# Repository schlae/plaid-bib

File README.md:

# The Plaid Bib - an Ad Lib MCA Clone

**This card uses the P82C611 bus interface chip and will not work with faster
MCA systems. For a more widely-compatible version, use the [Plaid Bib CPLD
version](https://github.com/schlae/plaid-bib-cpld).**

The Plaid Bib is a 100% compatible clone of the Ad Lib MCA sound card. This is
an Ad Lib card designed for Micro Channel Architecture machines, such as the
IBM PS/2 family and other compatibles from NCR, Tandy, Dell, and others.

Here are the design files. The BOM includes Mouser Electronics part numbers for
everything except for the 82C611, YM3812, and YM3014B, all of which are
available from brokers in China such as UTSource.

[Schematic](https://github.com/schlae/plaid-bib/blob/master/PlaidBib.pdf)

[Bill of Materials](https://github.com/schlae/plaid-bib/blob/master/PlaidBib.csv)

[Fab Files](https://github.com/schlae/plaid-bib/blob/master/fab/PlaidBib-fab.zip)

Use caution when obtaining the P82C611 MCA bus interface part. There is another
chip with the same part number from OPTi, except it is a VLB IDE controller and
totally different.

## Fabrication Notes
This is a two-layer board, outer dimensions 6.452in x 3.475in (164mm x 88mm).
Thickness of the board is 0.063in (1.6mm). When ordering the board, specify
a card edge bevel of 20 degrees. The Dwgs.User layer includes a detail with
the dimensions of the bevel.

Ideally you should use selective gold plating for the edge fingers, but this
can get expensive for small orders. ENIG will work but the gold will rub off
pretty quickly.

For the soldermask color, pick whatever you want! The original was green.

## Assembly Notes
You may wish to socket U7, U8, and U4. These sockets are not included in the
BOM. U7 and U8 are the Yamaha synthesizer chips, and it is useful to be able
to swap them out in case you get a bad one. U4 is the PAL; consider using a
socket in case of programming difficulties.

## PAL Notes
There is a programmable logic device that implements the address decoder and an
address bit latch. The original card uses a 16L8, but the Plaid Bib uses a
readily-available Atmel ATF16V8B. Here is the
[WinCUPL source](https://github.com/schlae/plaid-bib/blob/master/pld/plaidbib.pld)
and the resulting 
[JEDEC file](https://github.com/schlae/plaid-bib/blob/master/pld/plaidbib.jed).
You will need a device programmer such as the low-cost TL866A/CS. 

## Bracket
MCA brackets are no longer available. You have a few options:
- Remove the bracket from an existing card, like a token ring card or something
- 3D print the bracket
- Use the card without a bracket at all

If you want to print your own, here are STEP models of the bracket and the
plastic clip.

[Bracket](https://github.com/schlae/plaid-bib/blob/master/mech/MCABracket.STEP)

[Clip](https://github.com/schlae/plaid-bib/blob/master/mech/MCAClip.STEP)

Please note that neither file is designed specifically for 3D printing; they're
meant to match the real hardware exactly. The clip might print just fine, but
the bracket is probably too thin to print well.

## Compatibility

Micro Channel machines operate at a variety of different bus speeds. Only the
slower ones are compatible with the Plaid Bib.

|PS/2 Model|Clock t(ns)|Default transfer(ns)|Extended transfer(ns)| Compatible?|
|-----|-----------|--------------------|---------------------|----------------|
| 50  | 100       | 300/1WS (I/O)      | 300/1WS             | Yes |
| 55  | 62.5      | 250/2WS            | 375/4WS             | Untested |
| 60  | 100       | 300/1WS (I/O)      | 300/1WS             | Yes/untested |
| 65  | 62.5      | 250/2WS            | 375/4WS             | Untested |
| 70  | 50        | 200/2WS            | 300/4WS             | No |
| 80  | 62.5, 50, 40 | 200             | 300                 | No |
| 90  | 40        | 200                | 300                 | No |
| 95  | 40, 30    | 200, 240           | 300, 320            | No |

The YM3812 FM synthesis chip has minimum timings that are somewhat too slow.
For example, the read pulse width minimum spec is 200ns. The 82C611 generates
the read pulse based on the MCA CMD signal, which asserts for only part of the
default transfer cycle. A fast machine like the model 90 has a default transfer
cycle time of 200ns, so CMD is low for only about 90ns. This is too short to
properly read from the FM chip, meaning that Ad Lib auto detect functions will
fail to see the card.

## Installation
You will need the ADF (adapter description file) in order to set up the Plaid
Bib on your MCA computer.

[Plaid Bib ADF](https://github.com/schlae/plaid-bib/blob/master/@70D7.ADF)

Place the file on a 3 1/2" floppy disk. After you install the card and boot
the computer, it will detect that a new card has been installed and prompt
you to insert the reference disk. Do this and follow the prompts. When the
setup utility asks you to insert the option disk, use the one that contains
the ADF file. After the setup utility configures the card, it will prompt
you to reboot the machine.

Once that's finished, try out the Plaid Bib with your favorite game!

## License
This work is licensed under a Creative Commons Attribution-ShareAlike 4.0
International License. See [https://creativecommons.org/licenses/by-sa/4.0/](https://creativecommons.org/licenses/by-sa/4.0/).

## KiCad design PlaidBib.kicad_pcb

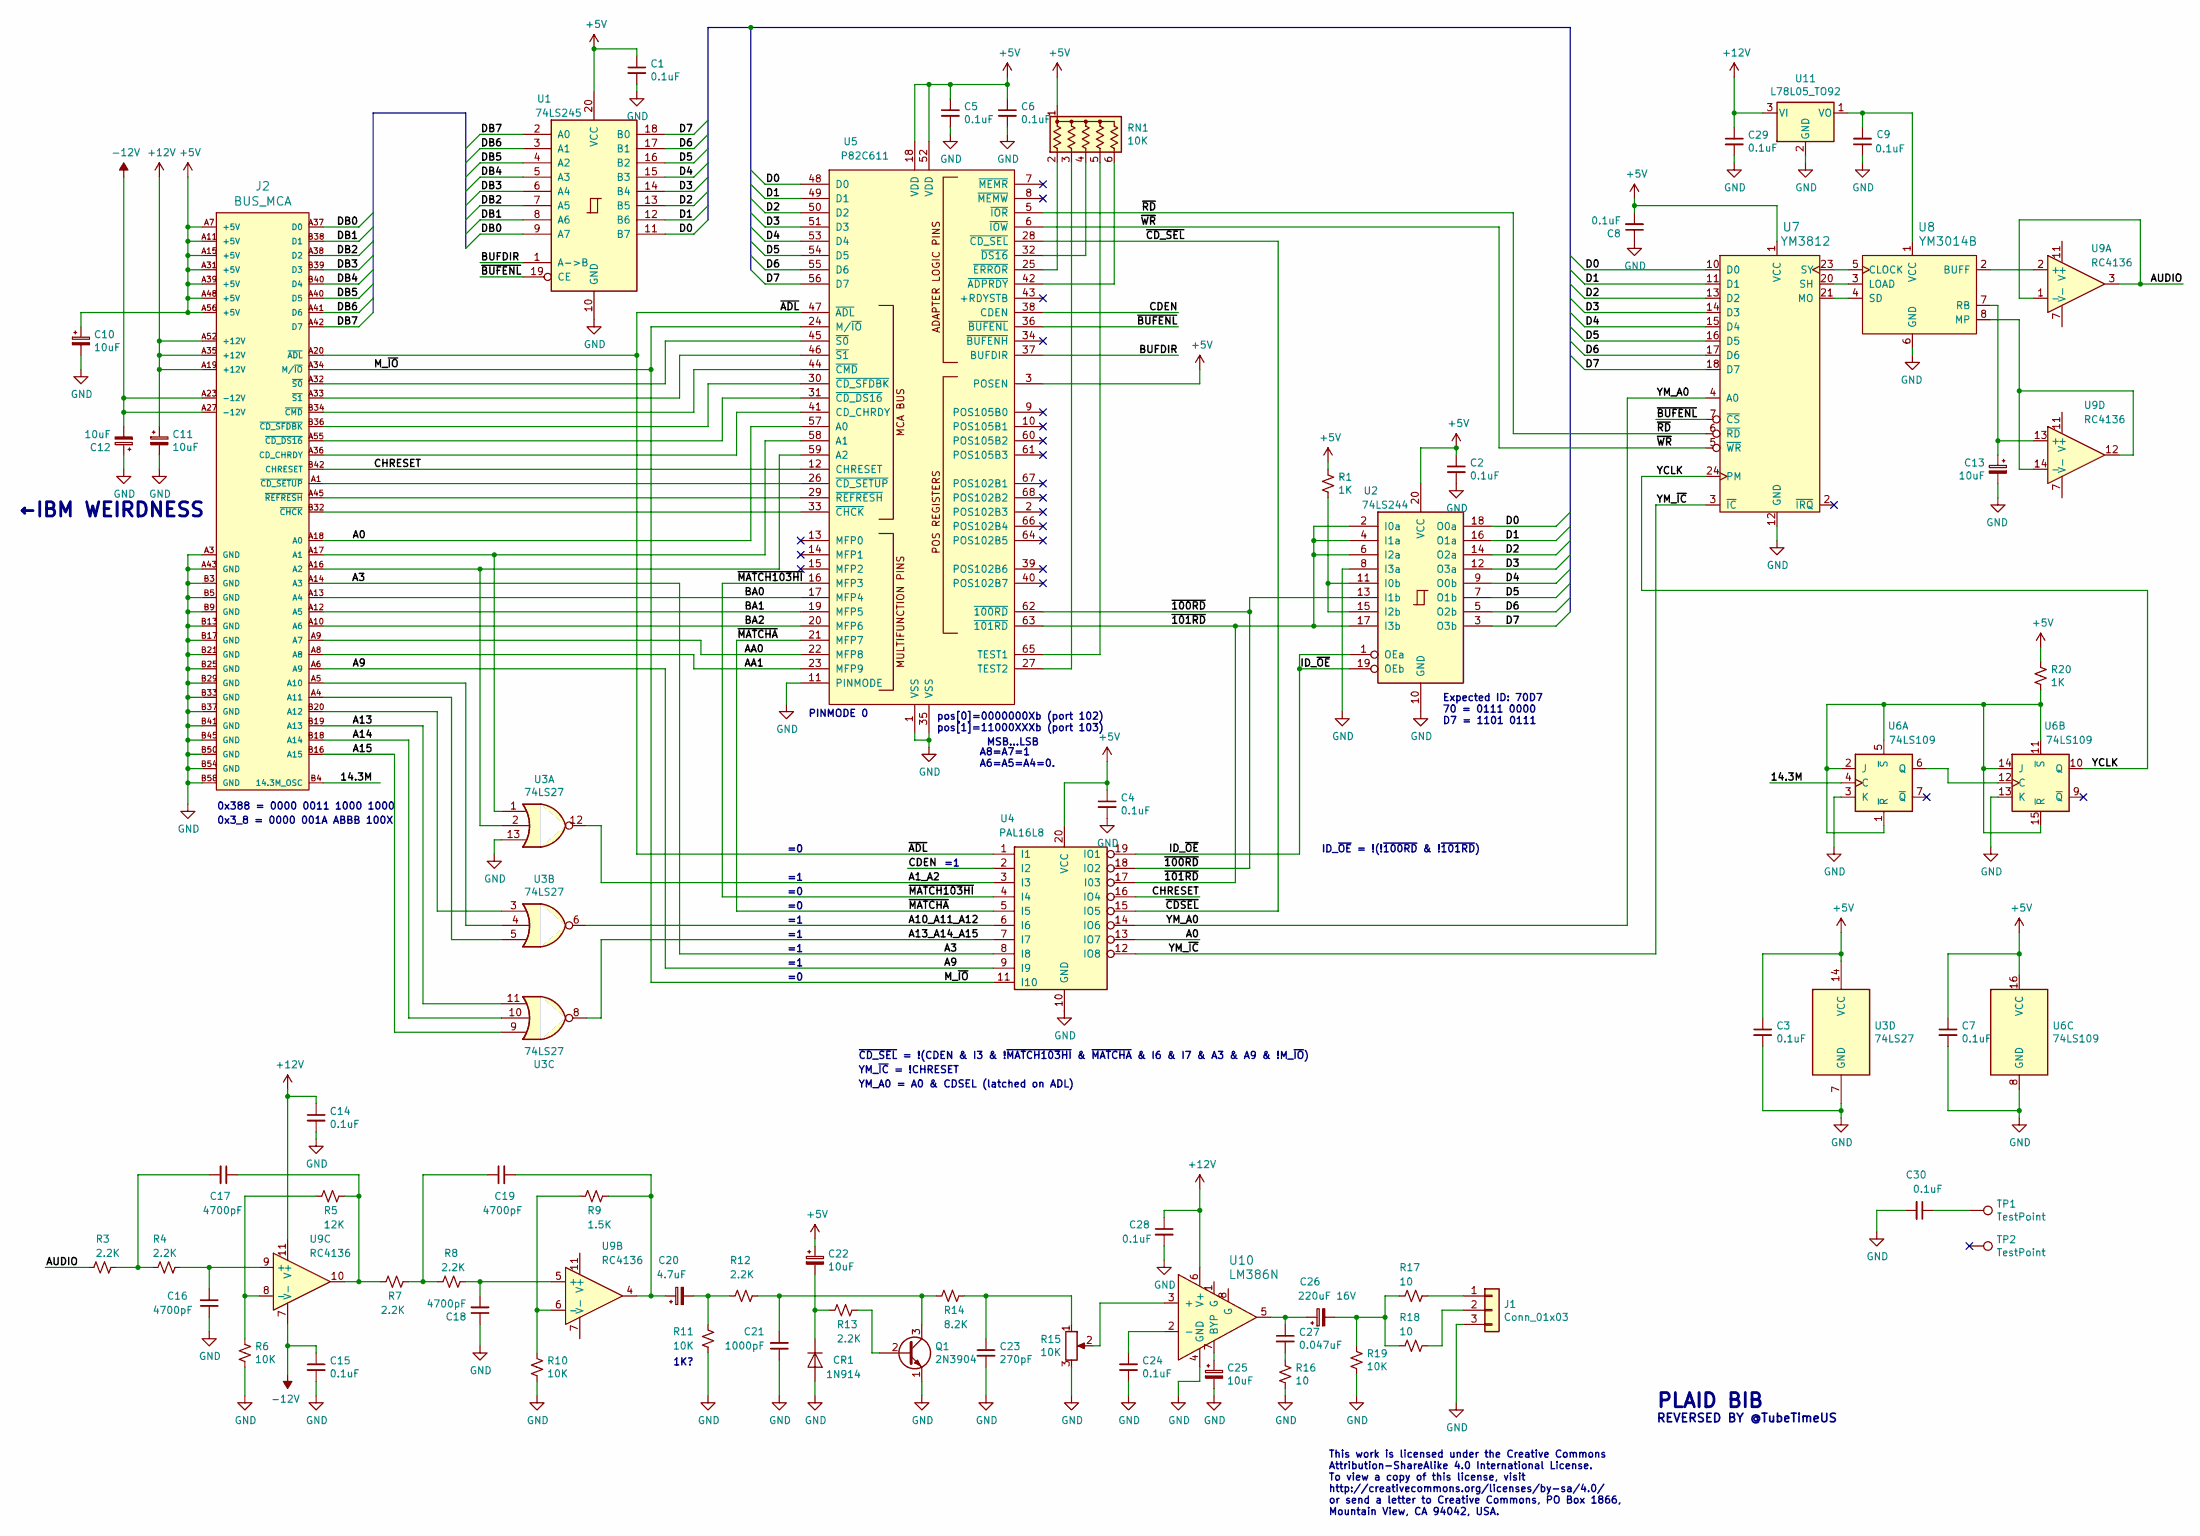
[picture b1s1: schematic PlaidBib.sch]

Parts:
C1, C2, C3, C4, C5, C6, C7, C8, C9, C14, C15, C24, C28, C29, C30: 0.1uF; CAP23; Mouser 581-AR215C104K4R
C10, C11, C12, C13, C22, C25: 10uF; CAPAP200; Mouser 581-TAP106M025CRW
C16, C17, C18, C19: 4700pF; CAP23; Mouser 581-AR211C472K4R
C20: 4.7uF; CAPAP200; Mouser 581-TAP475K016SCS
C21: 1000pF; CAP23; Mouser 581-AR211C102K4R
C23: 270pF; CAP23; Mouser 594-S271K43SL0N6TK5R
C26: 220uF 16V; CAPA1000; Mouser 647-TVX1C221MAD
C27: 0.047uF; CAP23; Mouser 581-AR215C473K4R
CR1: 1N914; DIOA500; Mouser 512-1N914
J1: Conn_01x03; SJ1-3553; Mouser 490-SJ1-3553NG
J2: BUS_MCA; BUS_MCA_ADLIB
Q1: 2N3904; TO92-IL; Mouser 512-2N3904BU
R1, R20: 1K; RESA500; Mouser 291-1K-RC
R3, R4, R7, R8, R12, R13: 2.2K; RESA500; Mouser 291-2.2K-RC
R5: 12K; RESA500; Mouser 291-12K-RC
R6, R10, R11, R19: 10K; RESA500; Mouser 291-10K-RC
R9: 1.5K; RESA500; Mouser 291-1.5K-RC
R14: 8.2K; RESA500; Mouser 291-8.2K-RC
R15: 10K; RK14J11A000G; Mouser 688-RK14J11A000G
R16, R17, R18: 10; RESA500; Mouser 291-10-RC
RN1: 10K; R_Array_SIP6; MPN 4606X-101-103LF; Mouser 652-4606X-1LF-10K
TP1, TP2: TestPoint; MH_125
U1: 74LS245; DIP300_20N; Mouser 595-SN74LS245N
U2: 74LS244; DIP300_20N; Mouser 595-SN74LS244N
U3: 74LS27; DIP300_14N; Mouser 595-SN74LS27N
U4: PAL16L8; DIP300_20N; Mouser 556-AF16V8B15PU
U5: P82C611; PLCC-68_THT-Socket
U6: 74LS109; DIP300_16N; Mouser 595-SN74LS109AN
U7: YM3812; DIP600_24N
U8: YM3014B; DIP300_8N
U9: RC4136; DIP300_14N; Mouser 595-RC4136N
U10: LM386N; DIP300_8N; Mouser 926-LM386N-4/NOPB
U11: L78L05_TO92; TO92-IL; Mouser 511-L78L05ACZ

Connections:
+5V: C1.1, C2.1, C3.1, C4.1, C5.1, C6.1, C7.1, C8.2, C10.1, C22.1, J2.A7 (+5V), J2.A11 (+5V), J2.A15 (+5V), J2.A31 (+5V), J2.A39 (+5V), J2.A48 (+5V), J2.A56 (+5V), R1.1, R20.1, RN1.1 (common), U1.20 (VCC), U2.20 (VCC), U3.14 (VCC), U4.20 (VCC), U5.3 (POSEN), U5.18 (VDD), U5.52 (VDD), U6.16 (VCC), U7.1 (VCC)
+12V: C11.1, C14.1, C28.1, C29.1, J2.A19 (+12V), J2.A35 (+12V), J2.A52 (+12V), U9.11 (V+), U10.6 (V+), U11.3 (VI)
-12V: C12.2, C15.1, J2.A23 (-12V), J2.A27 (-12V), U9.7 (V-)
/14.3M: J2.B4 (14.3M_OSC), U6.4 (C)
/A0: J2.A18 (A0), U4.13 (IO7), U5.57 (A0)
/A1_A2: U3.12, U4.3 (I3)
/A3: J2.A14 (A3), U4.8 (I8)
/A9: J2.A6 (A9), U4.9 (I9)
/A10_A11_A12: U3.6, U4.6 (I6)
/A13: J2.B19 (A13), U3.11
/A13_A14_A15: U3.8, U4.7 (I7)
/A14: J2.B18 (A14), U3.10
/A15: J2.B16 (A15), U3.9
/AA0: J2.A9 (A7), U5.22 (MFP8)
/AA1: J2.A8, U5.23 (MFP9)
/AUDIO: R3.2, U9.1 (-), U9.3
/BA0: J2.A13 (A4), U5.17 (MFP4)
/BA1: J2.A12 (A5), U5.19 (MFP5)
/BA2: J2.A10 (A6), U5.20 (MFP6)
/BUFDIR: U1.1 (A->B), U5.37 (BUFDIR)
/CDEN: U4.2 (I2), U5.38 (CDEN)
/CHRESET: J2.B42 (CHRESET), U4.16 (IO4), U5.12 (CHRESET)
/D0: U1.11 (B7), U2.18 (O0a), U5.48 (D0), U7.10 (D0)
/D1: U1.12 (B6), U2.16 (O1a), U5.49 (D1), U7.11 (D1)
/D2: U1.13 (B5), U2.14 (O2a), U5.50 (D2), U7.13 (D2)
/D3: U1.14 (B4), U2.12 (O3a), U5.51 (D3), U7.14 (D3)
/D4: U1.15 (B3), U2.9 (O0b), U5.53 (D4), U7.15 (D4)
/D5: U1.16 (B2), U2.7 (O1b), U5.54 (D5), U7.16 (D5)
/D6: U1.17 (B1), U2.5 (O2b), U5.55 (D6), U7.17 (D6)
/D7: U1.18 (B0), U2.3 (O3b), U5.56 (D7), U7.18 (D7)
/DB0: J2.A37 (D0), U1.9 (A7)
/DB1: J2.B38 (D1), U1.8 (A6)
/DB2: J2.A38 (D2), U1.7 (A5)
/DB3: J2.B39 (D3), U1.6 (A4)
/DB4: J2.B40 (D4), U1.5 (A3)
/DB5: J2.A40 (D5), U1.4 (A2)
/DB6: J2.A41 (D6), U1.3 (A1)
/DB7: J2.A42 (D7), U1.2 (A0)
/ID_~OE: U2.1 (OEa), U2.19 (OEb), U4.19 (IO1)
/M_~IO: J2.A34 (M/~IO), U4.11 (I10), U5.24 (M/~IO)
/YCLK: U6.10 (Q), U7.24 (PM)
/YM_A0: U4.14 (IO6), U7.4 (A0)
/YM_~IC: U4.12 (IO8), U7.3 (~IC)
/~100RD: U2.13 (I1b), U4.18 (IO2), U5.62 (~100RD)
/~101RD: U2.2 (I0a), U2.4 (I1a), U2.6 (I2a), U2.17 (I3b), U4.17 (I03), U5.63 (~101RD)
/~ADL: J2.A20 (~ADL), U4.1 (I1), U5.47 (~ADL)
/~BUFENL: U1.19 (CE), U5.36 (~BUFENL), U7.7 (~CS)
/~CDSEL: U4.15 (IO5), U5.28 (~CD_SEL)
/~MATCH103HI: U4.4 (I4), U5.16 (MFP3)
/~MATCHA: U4.5 (I5), U5.21 (MFP7)
/~RD: U5.5 (~IOR), U7.6 (~RD)
/~WR: U5.6 (~IOW), U7.5 (~WR)
GND: C1.2, C2.2, C3.2, C4.2, C5.2, C6.2, C7.2, C8.1, C9.1, C10.2, C11.2, C12.1, C13.2, C14.2, C15.2, C16.2, C18.1, C21.1, C23.2, C24.2, C25.2, C28.2, C29.2, C30.2, CR1.2 (A), J1.3, J2.A3 (GND), J2.A43 (GND), J2.B3 (GND), J2.B5 (GND), J2.B9 (GND), J2.B13 (GND), J2.B17 (GND), J2.B21 (GND), J2.B25 (GND), J2.B29 (GND), J2.B33 (GND), J2.B37 (GND), J2.B41 (GND), J2.B45 (GND), J2.B50 (GND), J2.B54 (GND), J2.B58 (GND), Q1.1 (E), R6.2, R10.2, R11.2, R15.3, R16.2, R19.2, U1.10 (GND), U2.8 (I3a), U2.10 (GND), U3.7 (GND), U3.13, U4.10 (GND), U5.1 (VSS), U5.11 (PINMODE), U5.35 (VSS), U6.3 (K), U6.8 (GND), U6.13 (K), U7.12 (GND), U8.6 (GND), U10.4 (GND), U11.2 (GND)
unnamed: C9.2, U8.1 (VCC), U11.1 (VO)
unnamed: C13.1, U8.7 (RB), U9.13 (+)
unnamed: C16.1, R4.1, U9.9 (+)
unnamed: C17.1, R5.1, R7.2, U9.10
unnamed: C17.2, R3.1, R4.2
unnamed: C18.2, R8.2, U9.5 (+)
unnamed: C19.1, R7.1, R8.1
unnamed: C19.2, C20.1, R9.1, U9.4
unnamed: C20.2, R11.1, R12.2
unnamed: C21.2, Q1.3 (C), R12.1, R14.2
unnamed: C22.2, CR1.1 (K), R13.2
unnamed: C23.1, R14.1, R15.1
unnamed: C24.1, U10.2 (-)
unnamed: C25.1, U10.7 (BYP)
unnamed: C26.1, C27.1, U10.5
unnamed: C26.2, R17.1, R18.1, R19.1
unnamed: C27.2, R16.1
unnamed: C30.1, TP1.1
unnamed: J1.1, R17.2
unnamed: J1.2, R18.2
unnamed: J2.A1 (~CD_SETUP), U5.26 (~CD_SETUP)
unnamed: J2.A4 (A11), U3.5
unnamed: J2.A5 (A10), U3.4
unnamed: J2.A16 (A2), U3.2, U5.59 (A2)
unnamed: J2.A17 (A1), U3.1, U5.58 (A1)
unnamed: J2.A32 (~S0), U5.45 (~S0)
unnamed: J2.A33 (~S1), U5.46 (~S1)
unnamed: J2.A36 (CD_CHRDY), U5.41 (CD_CHRDY)
unnamed: J2.A45 (~REFRESH), U5.29 (~REFRESH)
unnamed: J2.A55 (~CD_DS16), U5.31 (~CD_DS16)
unnamed: J2.B20 (A12), U3.3
unnamed: J2.B32 (~CHCK), U5.33 (~CHCK)
unnamed: J2.B34 (~CMD), U5.44 (~CMD)
unnamed: J2.B36 (~CD_SFDBK), U5.30 (~CD_SFDBK)
unnamed: Q1.2 (B), R13.1
unnamed: R1.2, U2.11 (I0b), U2.15 (I2b)
unnamed: R5.2, R6.1, U9.8 (-)
unnamed: R9.2, R10.1, U9.6 (-)
unnamed: R15.2, U10.3 (+)
unnamed: R20.2, U6.1 (~R), U6.2 (J), U6.5 (~S), U6.11 (~S), U6.14 (J), U6.15 (~R)
unnamed: RN1.2 (R1), U5.25 (~ERROR)
unnamed: RN1.3 (R2), U5.27 (TEST2)
unnamed: RN1.4 (R3), U5.32 (~DS16)
unnamed: RN1.5 (R4), U5.65 (TEST1)
unnamed: RN1.6 (R5), U5.42 (~ADPRDY)
unnamed: U6.6 (Q), U6.12 (C)
unnamed: U7.20 (SH), U8.3 (LOAD)
unnamed: U7.21 (MO), U8.4 (SD)
unnamed: U7.23 (SY), U8.5 (CLOCK)
unnamed: U8.2 (BUFF), U9.2 (+)
unnamed: U8.8 (MP), U9.12, U9.14 (-)

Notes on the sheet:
Expected ID: 70D7 70 = 0111 0000 D7 = 1101 0111
0x388 = 0000 0011 1000 1000
1K?
pos[0]=0000000Xb (port 102) pos[1]=11000XXXb (port 103)
MSB...LSB
A8=A7=1 A6=A5=A4=0.
PINMODE 0
←IBM WEIRDNESS
0x3_8 = 0000 001A ABBB 100X
ID_~OE~ = !(!~100RD~ & !~101RD~)
~CD_SEL~ = !(CDEN & I3 & !~MATCH103HI~ & ~MATCHA~ & I6 & I7 & A3 & A9 & !M_~IO~)
YM_~IC~ = !CHRESET
YM_A0 = A0 & CDSEL (latched on ADL)
PLAID BIB
REVERSED BY @TubeTimeUS
This work is licensed under the Creative Commons Attribution-ShareAlike 4.0 International License. To view a copy of this license, visit http://creativecommons.org/licenses/by-sa/4.0/ or send a letter to Creative Commons, PO Box 1866, Mountain View, CA 94042, USA.

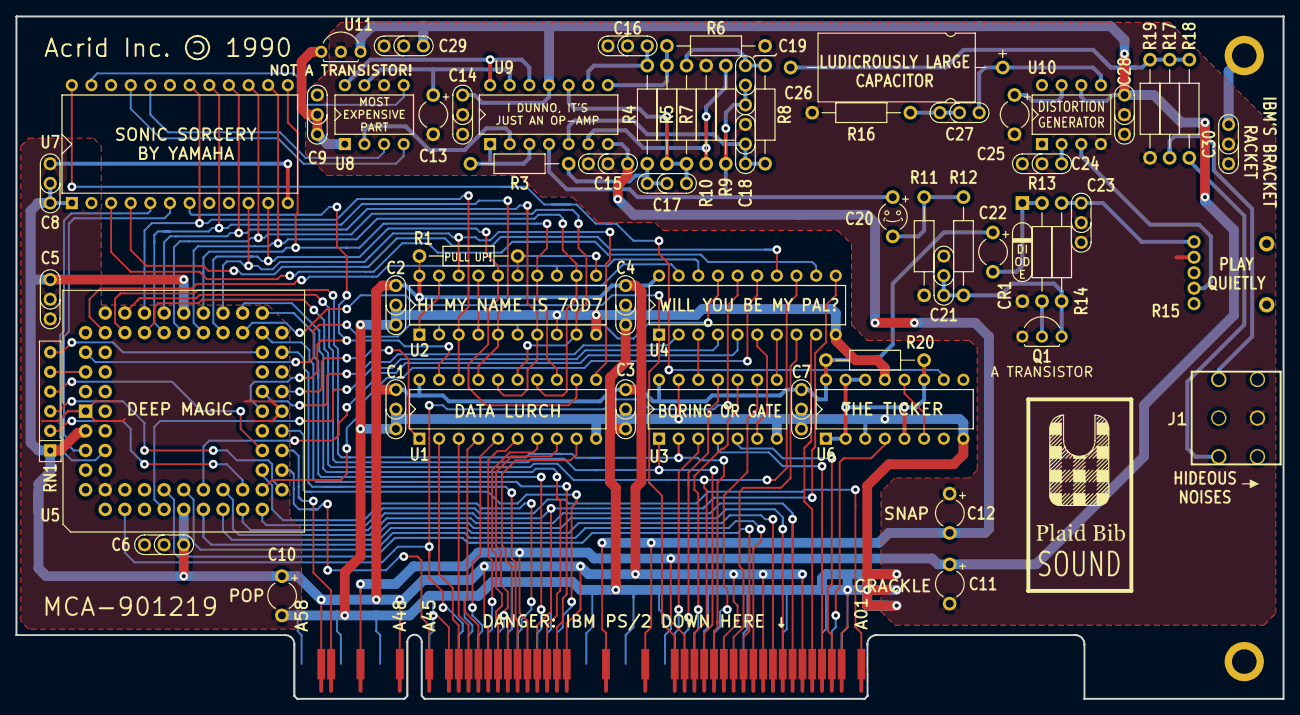
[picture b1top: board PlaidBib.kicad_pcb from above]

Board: 2 copper layers, 163.9 x 88.3 mm, 67 parts (0 on the bottom side), 104 nets.

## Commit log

2019-12-14 initial empty commit
2019-12-14 initial Plaid Bib files
2019-12-14 add STEP files for bracket
2019-12-15 add license to README.md
2020-01-08 Fix image
2020-01-09 update README to link to CPLD version

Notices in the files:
PlaidBib.kicad_pcb:
Copyright (C) 2019 Eric Schlaepfer
CC BY-SA (Attribution-ShareAlike)
